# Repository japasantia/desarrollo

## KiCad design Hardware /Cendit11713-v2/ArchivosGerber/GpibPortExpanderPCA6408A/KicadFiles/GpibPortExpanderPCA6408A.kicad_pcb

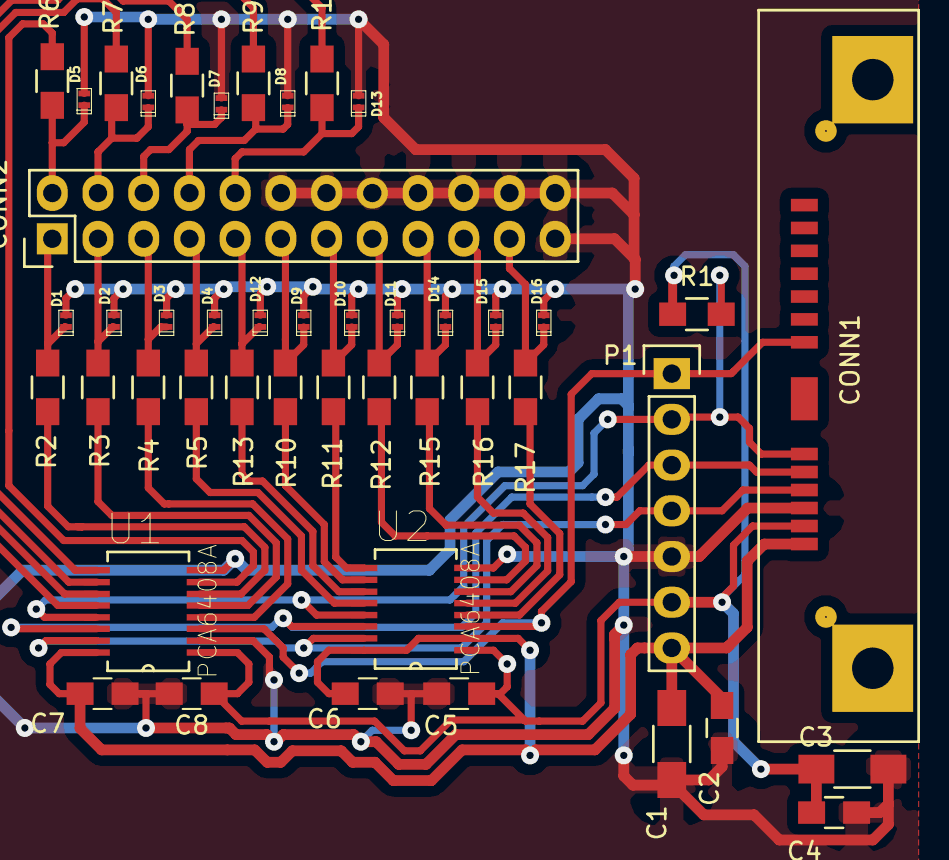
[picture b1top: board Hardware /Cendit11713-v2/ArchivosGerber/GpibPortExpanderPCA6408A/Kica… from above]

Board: 2 copper layers, 46 parts (0 on the bottom side), 39 nets.

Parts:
C1, C3: 1uF; C_1206_HandSoldering
C2, C4, C5, C6, C7, C8: 0.1uF; C_0805_HandSoldering
CONN1: I2C_BUS; SLIMLINE_SATA_PLUG_7P_6P
CONN2: GPIB_CONN; GPIB_HEADER_12X2P
D1, D2, D3, D4, D5, D6, D7, D8, D9, D10, D11, D12, D13, D14, D15, D16: SPHV24; SPHV24-SOD882
P1: CONN_01X07; Pin_Header_Straight_1x07
R1: R; R_0805_HandSoldering
R2, R3, R4, R5, R6, R7, R8, R9, R10, R11, R12, R13, R14, R15, R16, R17: RB; R_0805_HandSoldering
U1, U2: PCA6408A; PCA6408A-SOP16

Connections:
+3V3: C3.1, C4.1, C6.1, C8.1, CONN1.2, P1.6, R1.1, U1.1, U2.1
+5V: C1.1, C2.1, C5.1, C7.1, CONN1.1, P1.7, U1.16, U2.2, U2.16
//INT: CONN1.6, P1.2, R1.2, U1.13, U2.13
//RESET: CONN1.7, P1.1, U1.3, U2.3
/ATN: CONN2.21, D16.1, R17.1
/D0: CONN2.1, D1.1, R2.1
/D1: CONN2.3, D2.1, R3.1
/D2: CONN2.5, D3.1, R4.1
/D3: CONN2.7, D4.1, R5.1
/D4: CONN2.2, D5.1, R6.1
/D5: CONN2.4, D6.1, R7.1
/D6: CONN2.6, D7.1, R8.1
/D7: CONN2.8, D8.1, R9.1
/DAV: CONN2.11, D9.1, R10.1
/EOI: CONN2.9, D12.1, R13.1
/IFC: CONN2.17, D14.1, R15.1
/NDAC: CONN2.15, D11.1, R12.1
/NRFD: CONN2.13, D10.1, R11.1
/PATN: R17.2, U2.4
/PD0: R2.2, U1.6
/PD1: R3.2, U1.5
/PD2: R4.2, U1.4
/PD3: R5.2, U2.12
/PD4: R6.2, U1.7
/PD5: R7.2, U1.9
/PD6: R8.2, U1.10
/PD7: R9.2, U1.11
/PDAV: R12.2, U2.7
/PEOI: R13.2, U2.11
/PIFC: R15.2, U2.6
/PNDAC: R10.2, U2.10
/PNRFD: R11.2, U2.9
/PREN: R14.2, U1.12
/PSRQ: R16.2, U2.5
/REN: CONN2.10, D13.1, R14.1
/SCL: CONN1.5, P1.3, U1.14, U2.14
/SDA: CONN1.4, P1.4, U1.15, U2.15
/SRQ: CONN2.19, D15.1, R16.1
GNDD: C1.2, C2.2, C3.2, C4.2, C5.2, C6.2, C7.2, C8.2, CONN1.3, CONN2.12, CONN2.14, CONN2.16, CONN2.18, CONN2.20, CONN2.22, CONN2.23, CONN2.24, D1.2, D2.2, D3.2, D4.2, D5.2, D6.2, D7.2, D8.2, D9.2, D10.2, D11.2, D12.2, D13.2, D14.2, D15.2, D16.2, P1.5, U1.2, U1.8, U2.8

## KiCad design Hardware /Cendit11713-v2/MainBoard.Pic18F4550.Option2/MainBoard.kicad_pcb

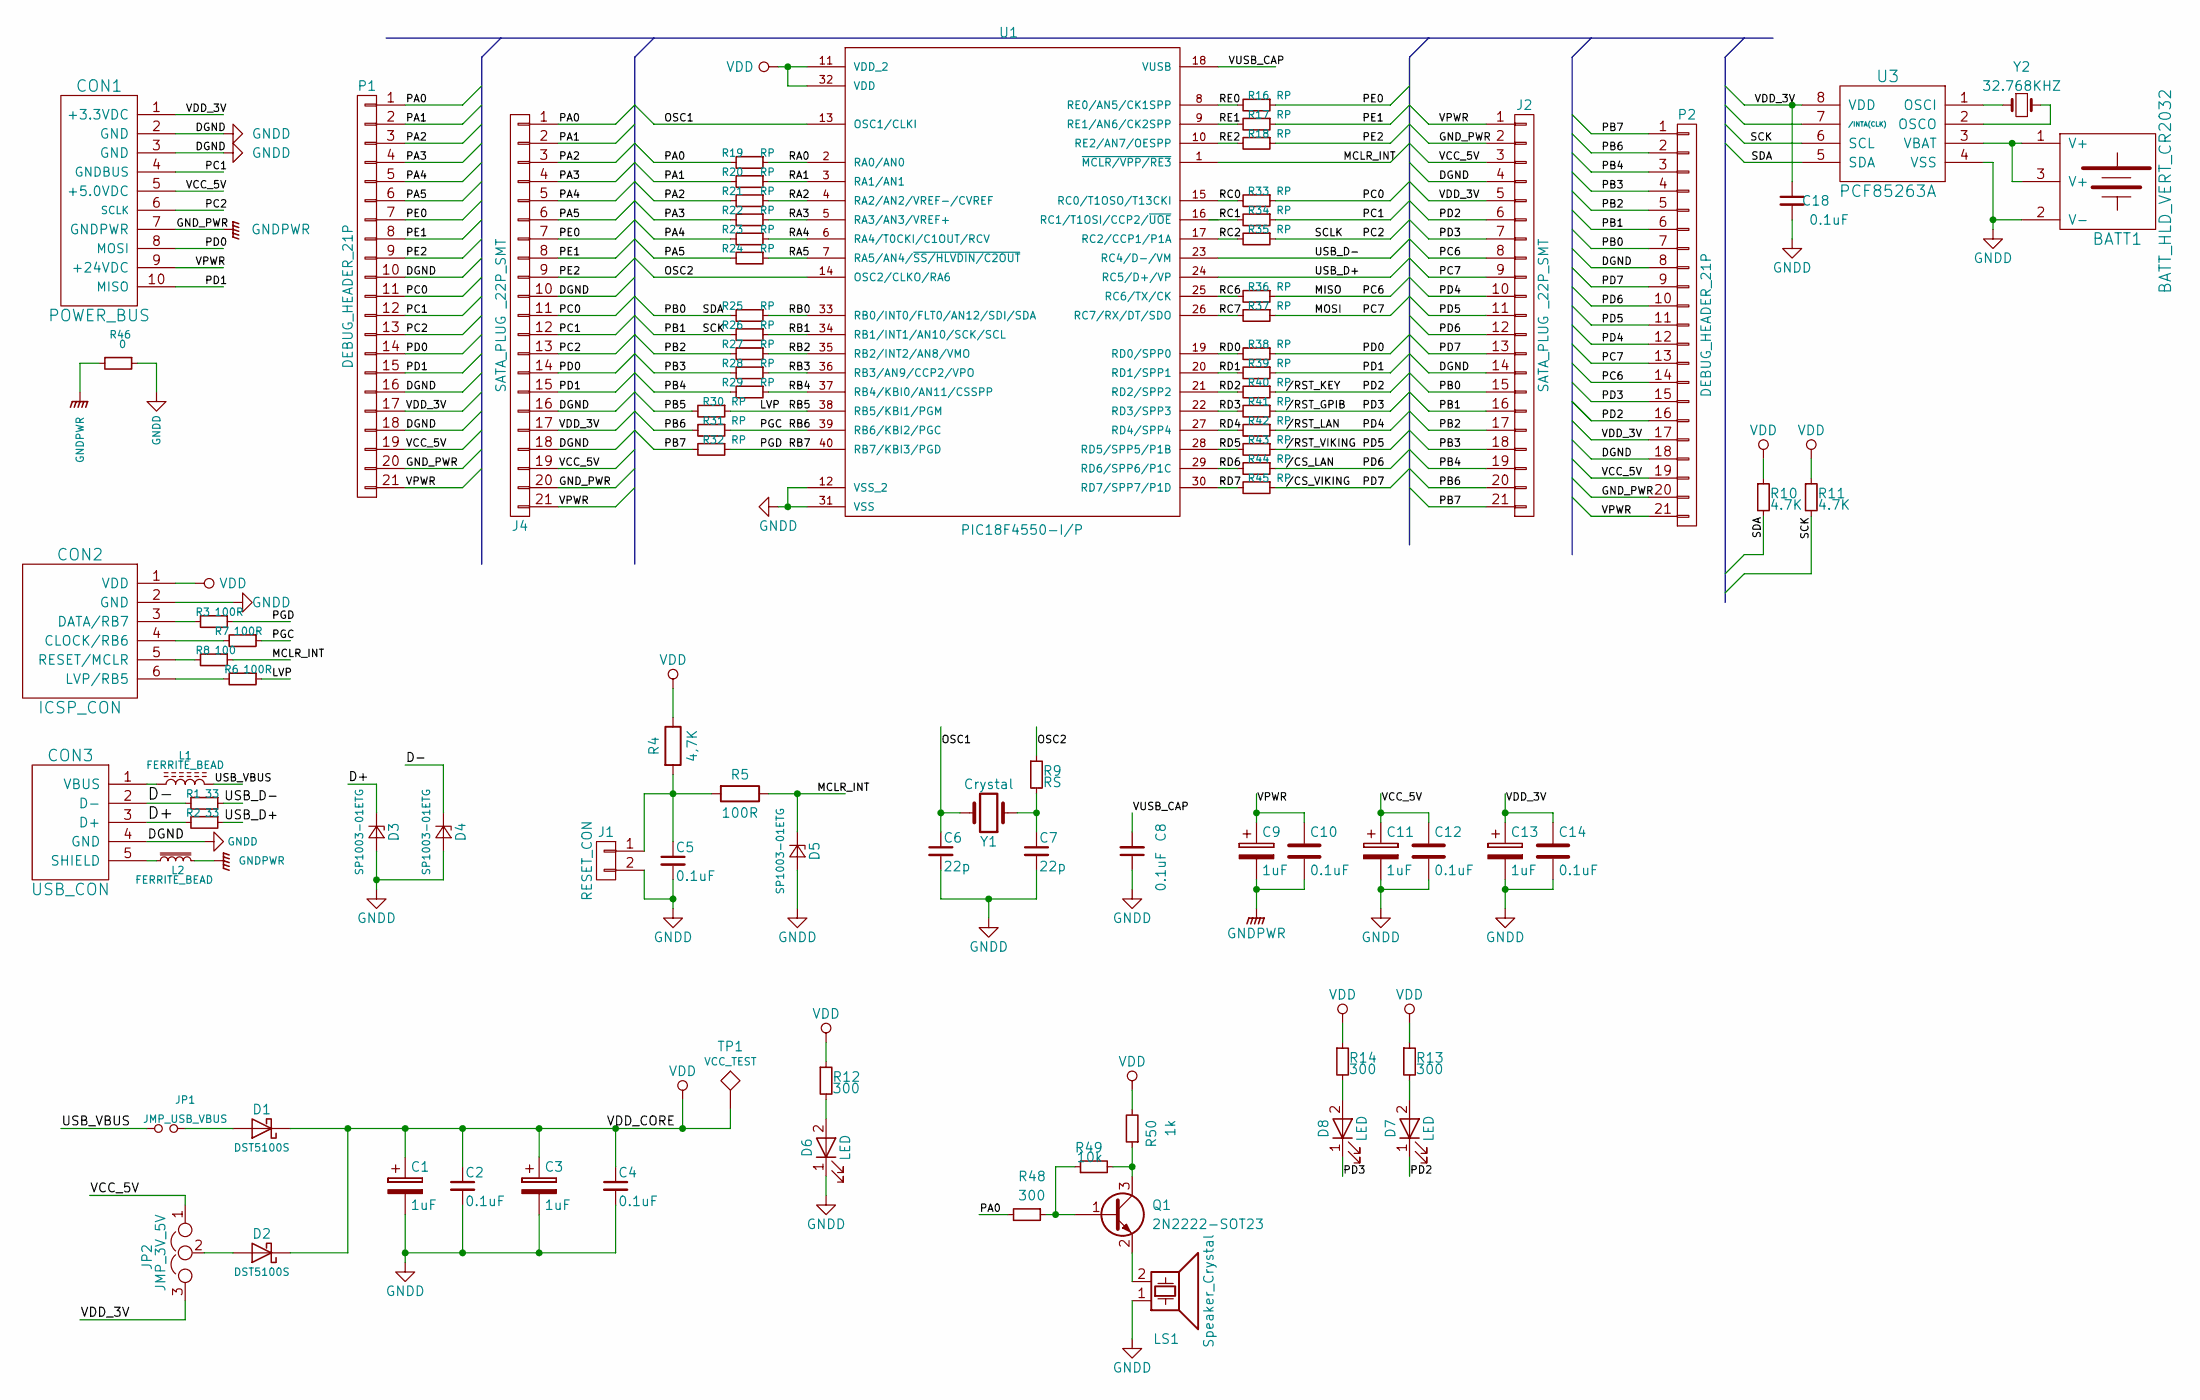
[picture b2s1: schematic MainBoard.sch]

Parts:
BATT1: BATT_HLD_VERT_CR2032; BATTERY_HOLDER_VERT_CR2032
C1, C3, C9, C11, C13: 1uF; C_1206_HandSoldering
C2, C4, C5, C10, C12, C14, C18: 0.1uF; C_0805_HandSoldering
C6, C7: 22p; C_0805_HandSoldering
C8: 0.1uF; C_1206_HandSoldering
CON1: POWER_BUS
CON2: ICSP_CON; Pin_Header_Straight_2x03
CON3: USB_CON; USB_SMT_B
D1, D2: DST5100S; DST5100S-TO-277B
D3, D4, D5: SP1003-01ETG
D6, D7, D8: LED; LED_0805
J1: RESET_CON; Pin_Header_Straight_1x02_Pitch2.54mm
J2, J4: SATA_PLUG _22P_SMT; SATA_PLUG_22P_SMT
JP1: JMP_USB_VBUS; Pin_Header_Straight_1x02_Pitch2.54mm
JP2: JMP_3V_5V; Pin_Header_Straight_1x03
L1, L2: FERRITE_BEAD; L_Axial_L5.3mm_D2.2mm_P2.54mm_Vertical_Vishay_IM-1
LS1: Speaker_Crystal; MagneticBuzzer_Kingstate_KCG0601
P1, P2: DEBUG_HEADER_21P; DEBUG_PIN_HEADER_21P
Q1: 2N2222-SOT23
R1, R2: 33; R_0603_HandSoldering
R3, R5, R6, R7: 100R; R_0805_HandSoldering
R4: 4,7K; R_0805_HandSoldering
R8: 100; R_0805_HandSoldering
R9: RS; R_0805_HandSoldering
R10, R11: 4.7K; R_0805_HandSoldering
R12, R13, R14: 300; R_0805_HandSoldering
R16, R17, R18, R19, R20, R21, R22, R23, R24, R25, R26, R27, R28, R29, R30, R31, R32, R33, R34, R35, R36, R37, R38, R39, R40, R41, R42, R43, R44, R45: RP; R_0805_HandSoldering
R46: 0; R_0805_HandSoldering
R48: 300; R_0603_HandSoldering
R49: 10k; R_0603_HandSoldering
R50: 1k; R_0603_HandSoldering
TP1: VCC_TEST
U1: PIC18F4550-I/P; PIC18F4550-PDIP
U3: PCF85263A; PCF85263A_SO8
Y1: Crystal; Crystal_HC49-4H_Vertical
Y2: 32.768KHZ; Crystal_C26-LF_d2.1mm_l6.5mm_Vertical

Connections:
//CS_LAN: J2.12, P2.10, R44.1
//CS_VIKING: J2.13, P2.9, R45.1
//RST_GPIB: D8.1 (K), J2.7, P2.15, R41.1
//RST_KEY: D7.1 (K), J2.6, P2.16, R40.1
//RST_LAN: J2.10, P2.12, R42.1
//RST_VIKING: J2.11, P2.11, R43.1
/D+: CON3.3 (D+), D3.1 (K), R2.2
/D-: CON3.2 (D-), D4.1 (K), R1.2
/LVP: R6.1, R30.1, U1.38 (RB5/KBI1/PGM)
/MCLR_INT: D5.1 (K), R5.1, R8.1, U1.1 (~MCLR/VPP/RE3)
/MISO: J2.8, P2.14, R36.1
/MOSI: J2.9, P2.13, R37.1
/OSC1: C6.1, U1.13 (OSC1/CLKI), Y1.2
/OSC2: R9.1, U1.14 (OSC2/CLKO/RA6)
/PA0: J4.1, P1.1, R19.2, R48.2
/PA1: J4.2, P1.2, R20.2
/PA2: J4.3, P1.3, R21.2
/PA3: J4.4, P1.4, R22.2
/PA4: J4.5, P1.5, R23.2
/PA5: J4.6, P1.6, R24.2
/PB0: J2.15, P2.7, R10.2, R25.2, U3.5 (SDA)
/PB1: J2.16, P2.6, R11.2, R26.2, U3.6 (SCL)
/PB2: J2.17, P2.5, R27.2
/PB3: J2.18, P2.4, R28.2
/PB4: J2.19, P2.3, R29.2
/PB5: R30.2
/PB6: J2.20, P2.2, R31.2
/PB7: J2.21, P2.1, R32.2
/PC0: J4.11, P1.11, R33.1
/PC1: CON1.4 (GNDBUS), J4.12, P1.12, R34.1
/PC2: CON1.6 (SCLK), J4.13, P1.13, R35.1
/PD0: CON1.8 (MOSI), J4.14, P1.14, R38.1
/PD1: CON1.10 (MISO), J4.15, P1.15, R39.1
/PE0: J4.7, P1.7, R16.1
/PE1: J4.8, P1.8, R17.1
/PE2: J4.9, P1.9, R18.1
/PGC: R7.1, R31.1, U1.39 (RB6/KBI2/PGC)
/PGD: R3.1, R32.1, U1.40 (RB7/KBI3/PGD)
/RA0: R19.1, U1.2 (RA0/AN0)
/RA1: R20.1, U1.3 (RA1/AN1)
/RA2: R21.1, U1.4 (RA2/AN2/VREF-/CVREF)
/RA3: R22.1, U1.5 (RA3/AN3/VREF+)
/RA4: R23.1, U1.6 (RA4/T0CKI/C1OUT/RCV)
/RA5: R24.1, U1.7 (RA5/AN4/~SS/HLVDIN/C2OUT)
/RB0: R25.1, U1.33 (RB0/INT0/FLT0/AN12/SDI/SDA)
/RB1: R26.1, U1.34 (RB1/INT1/AN10/SCK/SCL)
/RB2: R27.1, U1.35 (RB2/INT2/AN8/VMO)
/RB3: R28.1, U1.36 (RB3/AN9/CCP2/VPO)
/RB4: R29.1, U1.37 (RB4/KBI0/AN11/CSSPP)
/RC0: R33.2, U1.15 (RC0/T1OSO/T13CKI)
/RC1: R34.2, U1.16 (RC1/T1OSI/CCP2/~UOE)
/RC2: R35.2, U1.17 (RC2/CCP1/P1A)
/RC6: R36.2, U1.25 (RC6/TX/CK)
/RC7: R37.2, U1.26 (RC7/RX/DT/SDO)
/RD0: R38.2, U1.19 (RD0/SPP0)
/RD1: R39.2, U1.20 (RD1/SPP1)
/RD2: R40.2, U1.21 (RD2/SPP2)
/RD3: R41.2, U1.22 (RD3/SPP3)
/RD4: R42.2, U1.27 (RD4/SPP4)
/RD5: R43.2, U1.28 (RD5/SPP5/P1B)
/RD6: R44.2, U1.29 (RD6/SPP6/P1C)
/RD7: R45.2, U1.30 (RD7/SPP7/P1D)
/RE0: R16.2, U1.8 (RE0/AN5/CK1SPP)
/RE1: R17.2, U1.9 (RE1/AN6/CK2SPP)
/RE2: R18.2, U1.10 (RE2/AN7/OESPP)
/USB_D+: R2.1, U1.24 (RC5/D+/VP)
/USB_D-: R1.1, U1.23 (RC4/D-/VM)
/USB_VBUS: JP1.1, L1.2
/VCC_5V: C11.1, C12.1, CON1.5 (+5.0VDC), J2.3, J4.19, JP2.1, P1.19, P2.19
/VDD_3V: C13.1, C14.1, C18.1, CON1.1 (+3.3VDC), J2.5, J4.17, JP2.3, P1.17, P2.17, U3.8 (VDD)
/VPWR: C9.1, C10.1, CON1.9 (+24VDC), J2.1, J4.21, P1.21, P2.21
/VUSB_CAP: C8.2, U1.18 (VUSB)
GNDD: BATT1.2 (V-), C1.2, C2.2, C3.2, C4.2, C5.2, C6.2, C7.2, C8.1, C11.2, C12.2, C13.2, C14.2, C18.2, CON1.2 (GND), CON1.3 (GND), CON2.2 (GND), CON3.4 (GND), D3.2 (A), D4.2 (A), D5.2 (A), D6.1 (K), J1.2, J2.4, J2.14, J4.10, J4.16, J4.18, LS1.1, P1.10, P1.16, P1.18, P2.8, P2.18, R46.1, U1.12 (VSS_2), U1.31 (VSS), U3.4 (VSS)
GNDPWR: C9.2, C10.2, CON1.7 (GNDPWR), J2.2, J4.20, L2.2, P1.20, P2.20, R46.2
unnamed: BATT1.1 (V+), BATT1.3 (V+), U3.3 (VBAT)
unnamed: C5.1, J1.1, R4.2, R5.2
unnamed: C7.1, R9.2, Y1.1
unnamed: CON2.3 (DATA/RB7), R3.2
unnamed: CON2.4 (CLOCK/RB6), R7.2
unnamed: CON2.5 (RESET/MCLR), R8.2
unnamed: CON2.6 (LVP/RB5), R6.2
unnamed: CON3.1 (VBUS), L1.1
unnamed: CON3.5 (SHIELD), L2.1
unnamed: D1.2 (A), JP1.2
unnamed: D2.2 (A), JP2.2
unnamed: D6.2 (A), R12.2
unnamed: D7.2 (A), R13.2
unnamed: D8.2 (A), R14.2
unnamed: LS1.2, Q1.2 (E)
unnamed: Q1.1 (B), R48.1, R49.1
unnamed: Q1.3 (C), R49.2, R50.1
unnamed: U3.1 (OSCI), Y2.1
unnamed: U3.2 (OSCO), Y2.2
VDD: C1.1, C2.1, C3.1, C4.1, CON2.1 (VDD), D1.1 (K), D2.1 (K), R4.1, R10.1, R11.1, R12.1, R13.1, R14.1, R50.2, TP1.1, U1.11 (VDD_2), U1.32 (VDD)

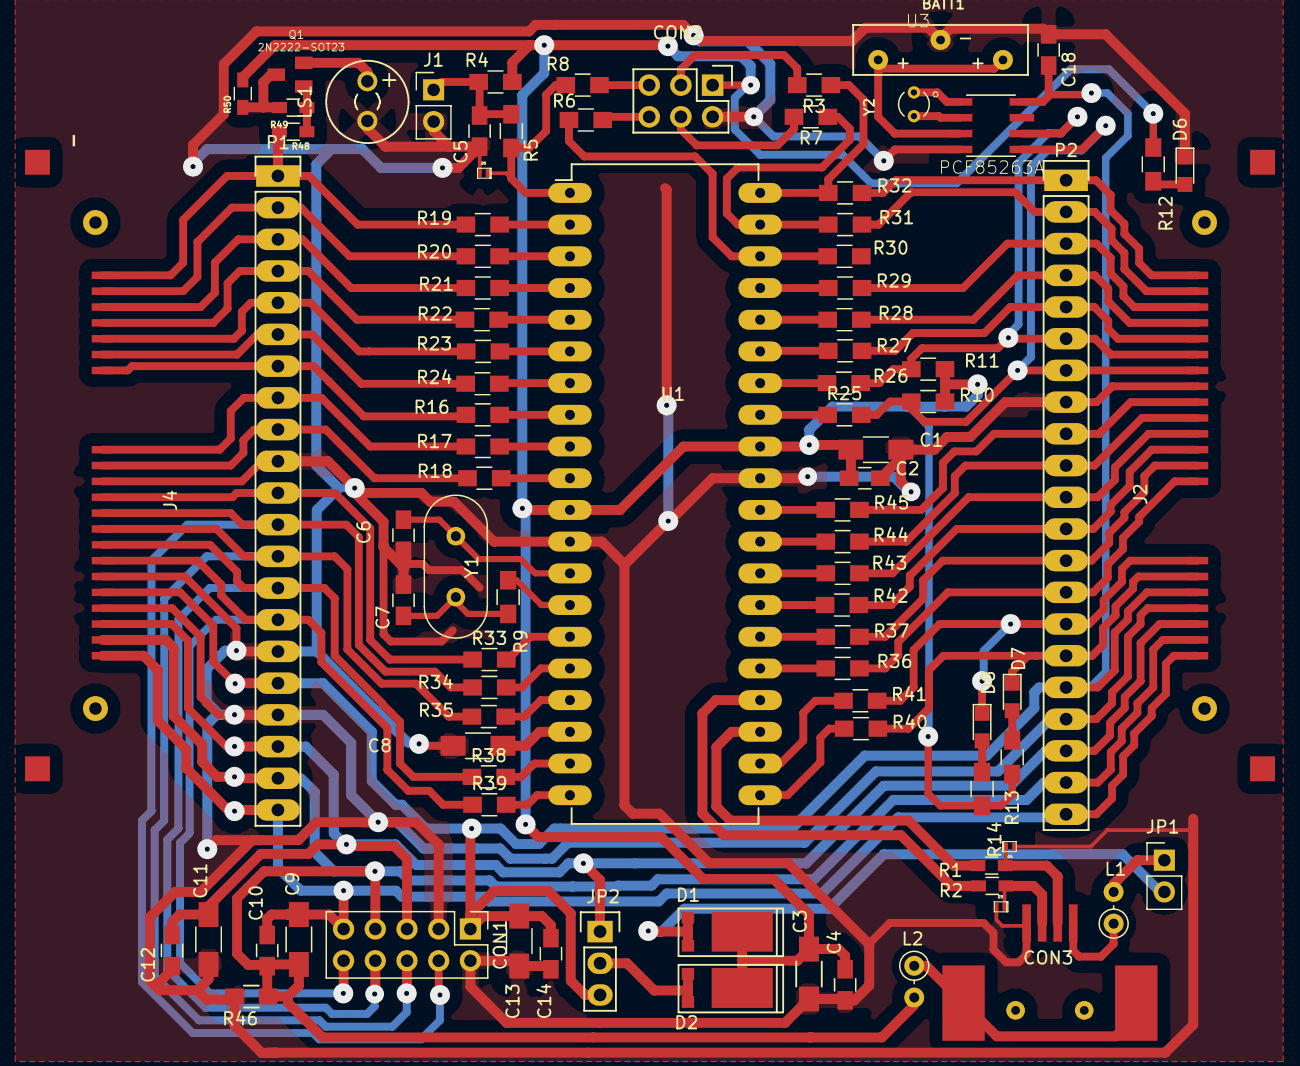
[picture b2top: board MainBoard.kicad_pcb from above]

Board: 2 copper layers, 90 parts (0 on the bottom side), 93 nets.

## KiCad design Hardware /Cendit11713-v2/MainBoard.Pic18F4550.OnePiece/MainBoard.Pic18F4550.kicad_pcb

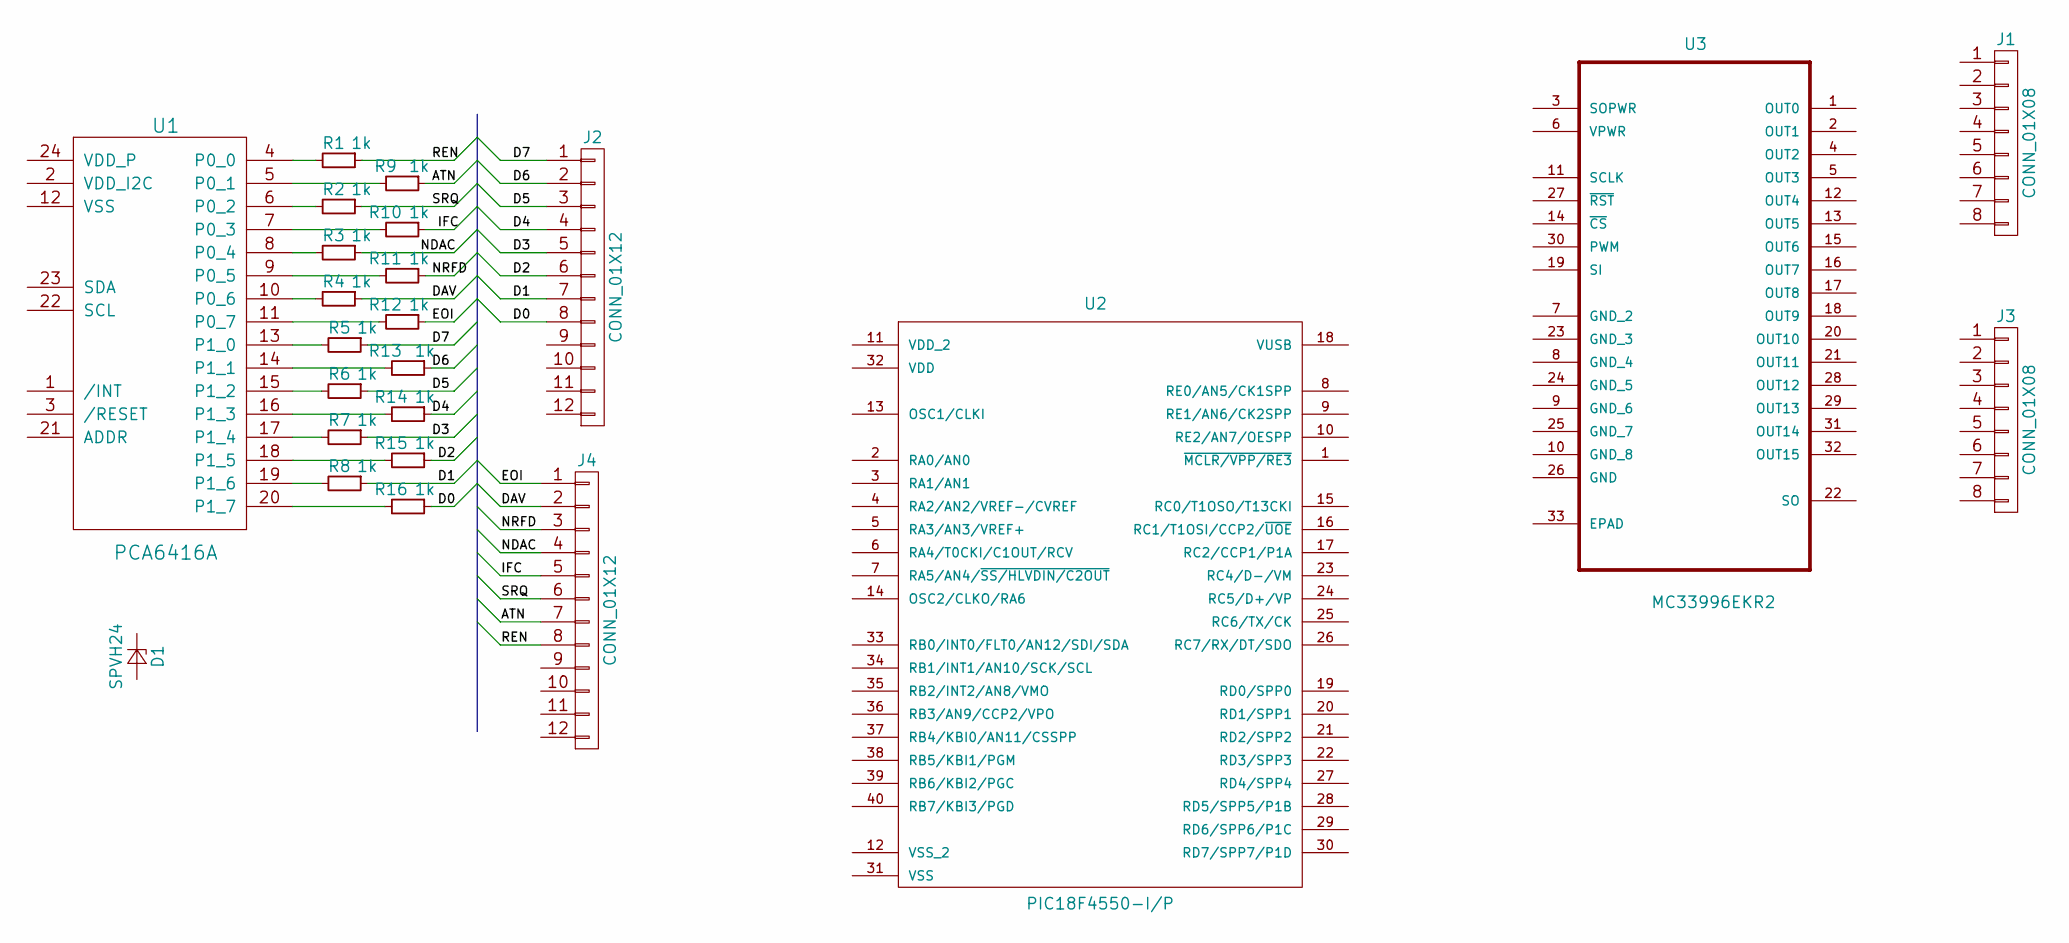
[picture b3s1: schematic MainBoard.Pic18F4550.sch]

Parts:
D1: SPVH24; SPHV24-SOD882
J1, J3: CONN_01X08; Pin_Header_Straight_1x08_Pitch2.54mm
J2, J4: CONN_01X12; Pin_Header_Straight_1x12_Pitch2.54mm
R1, R2, R3, R4, R5, R6, R7, R8, R9, R10, R11, R12, R13, R14, R15, R16: 1k; R_0805_HandSoldering
U1: PCA6416A; PCA6416A-TSSOP24
U2: PIC18F4550-I/P; PIC18F4550-PDIP
U3: MC33996EKR2; MC33996-SOIC32

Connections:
/ATN: J4.7, R9.1
/D0: J2.8, R16.1
/D1: J2.7, R8.1
/D2: J2.6, R15.1
/D3: J2.5, R7.1
/D4: J2.4, R14.1
/D5: J2.3, R6.1
/D6: J2.2, R13.1
/D7: J2.1, R5.1
/DAV: J4.2, R4.1
/EOI: J4.1, R12.1
/IFC: J4.5, R10.1
/NDAC: J4.4, R3.1
/NRFD: J4.3, R11.1
/REN: J4.8, R1.1
/SRQ: J4.6, R2.1
unnamed: R1.2, U1.4 (P0_0)
unnamed: R2.2, U1.6 (P0_2)
unnamed: R3.2, U1.8 (P0_4)
unnamed: R4.2, U1.10 (P0_6)
unnamed: R5.2, U1.13 (P1_0)
unnamed: R6.2, U1.15 (P1_2)
unnamed: R7.2, U1.17 (P1_4)
unnamed: R8.2, U1.19 (P1_6)
unnamed: R9.2, U1.5 (P0_1)
unnamed: R10.2, U1.7 (P0_3)
unnamed: R11.2, U1.9 (P0_5)
unnamed: R12.2, U1.11 (P0_7)
unnamed: R13.2, U1.14 (P1_1)
unnamed: R14.2, U1.16 (P1_3)
unnamed: R15.2, U1.18 (P1_5)
unnamed: R16.2, U1.20 (P1_7)

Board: 2 copper layers, 24 parts (0 on the bottom side), 32 nets, no tracks yet.

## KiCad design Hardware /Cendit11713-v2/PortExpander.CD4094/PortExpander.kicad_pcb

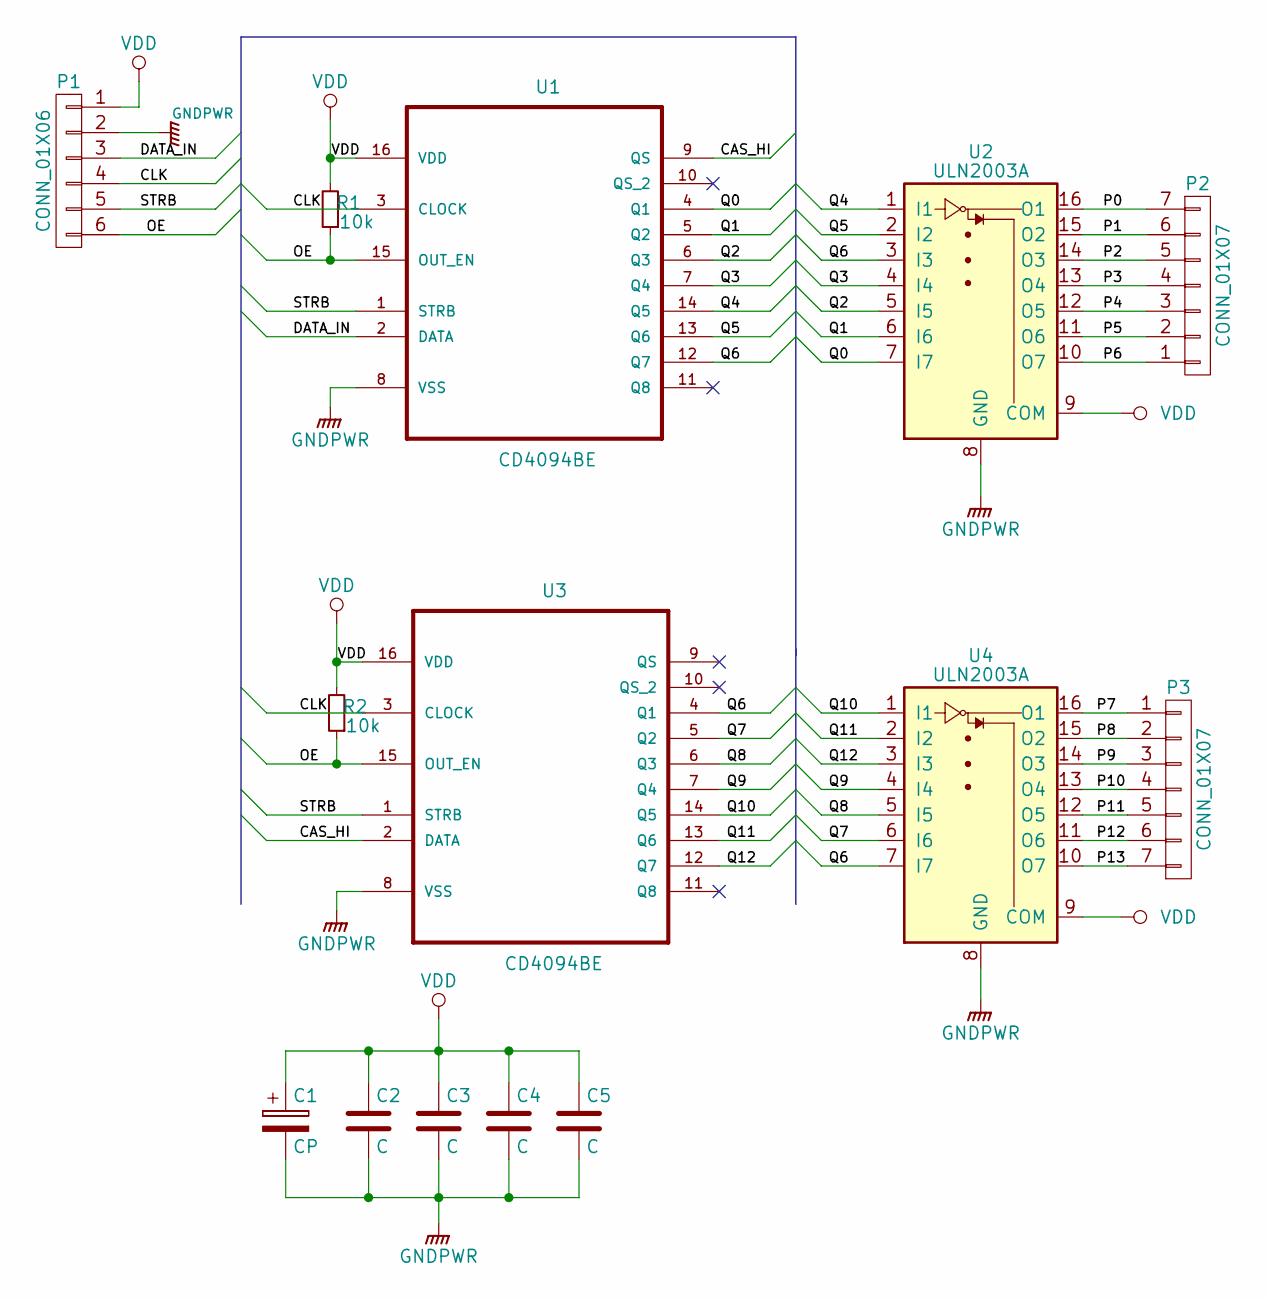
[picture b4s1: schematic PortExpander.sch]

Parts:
C1: CP; C_0805_HandSoldering
C2, C3, C4, C5: C; C_0805_HandSoldering
P1: CONN_01X06; Pin_Header_Straight_1x06
P2, P3: CONN_01X07; Pin_Header_Straight_1x07
R1, R2: 10k; R_0805_HandSoldering
U1, U3: CD4094BE; CD4094-DIP16
U2, U4: ULN2003A; ULN2003-DIP16

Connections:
/CAS_HI: U1.9 (QS), U3.2 (DATA)
/CLK: P1.4, U1.3 (CLOCK), U3.3 (CLOCK)
/DATA_IN: P1.3, U1.2 (DATA)
/OE: P1.6, R1.1, R2.1, U1.15 (OUT_EN), U3.15 (OUT_EN)
/P0: P2.7, U2.16 (O1)
/P1: P2.6, U2.15 (O2)
/P2: P2.5, U2.14 (O3)
/P3: P2.4, U2.13 (O4)
/P4: P2.3, U2.12 (O5)
/P5: P2.2, U2.11 (O6)
/P6: P2.1, U2.10 (O7)
/P7: P3.1, U4.16 (O1)
/P8: P3.2, U4.15 (O2)
/P9: P3.3, U4.14 (O3)
/P10: P3.4, U4.13 (O4)
/P11: P3.5, U4.12 (O5)
/P12: P3.6, U4.11 (O6)
/P13: P3.7, U4.10 (O7)
/Q0: U1.4 (Q1), U2.7 (I7)
/Q1: U1.5 (Q2), U2.6 (I6)
/Q2: U1.6 (Q3), U2.5 (I5)
/Q3: U1.7 (Q4), U2.4 (I4)
/Q4: U1.14 (Q5), U2.1 (I1)
/Q5: U1.13 (Q6), U2.2 (I2)
/Q6: U1.12 (Q7), U2.3 (I3), U3.4 (Q1), U4.7 (I7)
/Q7: U3.5 (Q2), U4.6 (I6)
/Q8: U3.6 (Q3), U4.5 (I5)
/Q9: U3.7 (Q4), U4.4 (I4)
/Q10: U3.14 (Q5), U4.1 (I1)
/Q11: U3.13 (Q6), U4.2 (I2)
/Q12: U3.12 (Q7), U4.3 (I3)
/STRB: P1.5, U1.1 (STRB), U3.1 (STRB)
GNDPWR: C1.2, C2.2, C3.2, C4.2, C5.2, P1.2, U1.8 (VSS), U2.8 (GND), U3.8 (VSS), U4.8 (GND)
VDD: C1.1, C2.1, C3.1, C4.1, C5.1, P1.1, R1.2, R2.2, U1.16 (VDD), U2.9 (COM), U3.16 (VDD), U4.9 (COM)

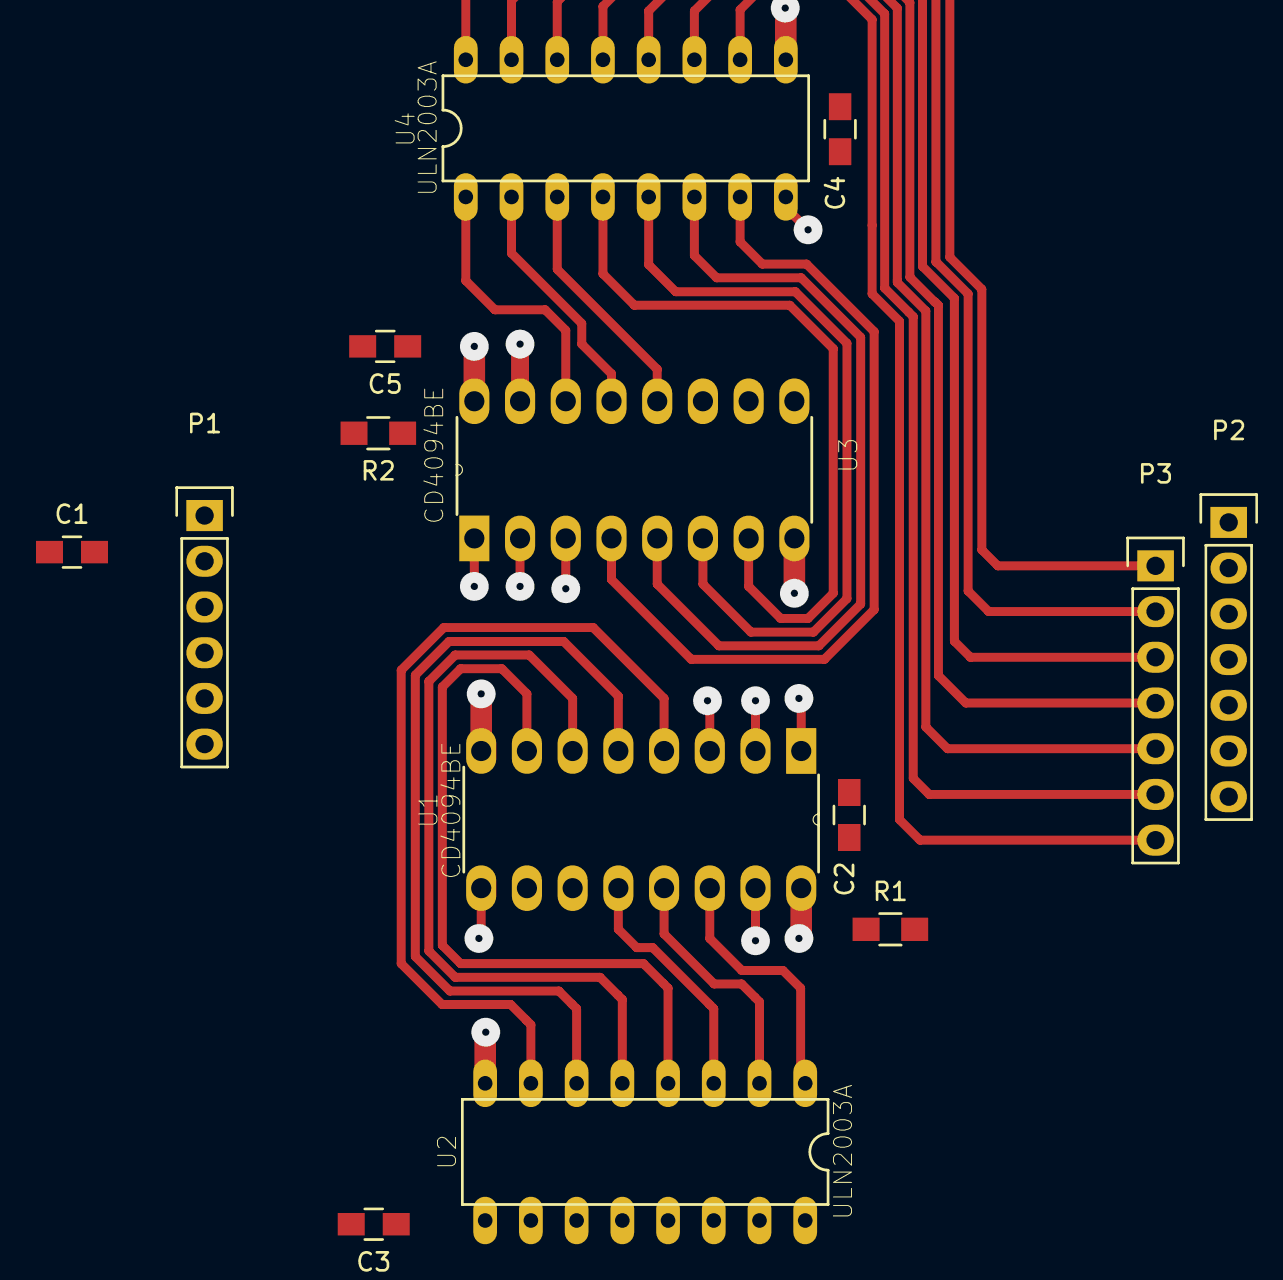
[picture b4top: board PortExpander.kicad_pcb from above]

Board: 2 copper layers, 14 parts (0 on the bottom side), 34 nets.

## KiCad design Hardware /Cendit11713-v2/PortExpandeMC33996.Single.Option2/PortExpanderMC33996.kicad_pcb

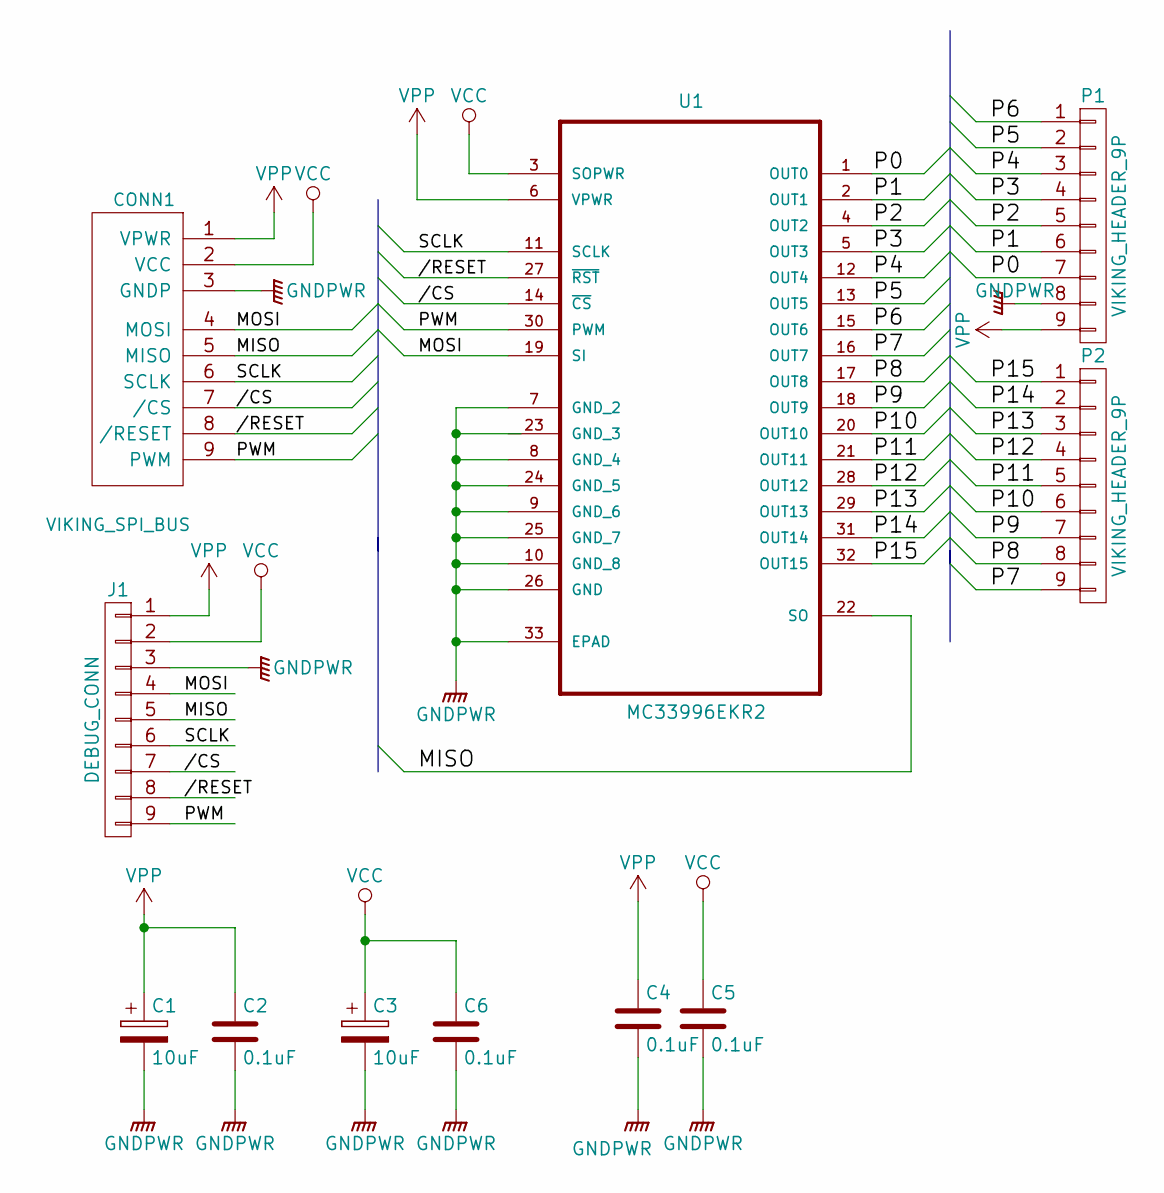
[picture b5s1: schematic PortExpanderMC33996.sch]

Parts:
C1, C3: 10uF; C_1206_HandSoldering
C2, C4, C5, C6: 0.1uF; C_0805_HandSoldering
CONN1: VIKING_SPI_BUS; SLIMLINE_SATA_PLUG_7P_6P
J1: DEBUG_CONN; Pin_Header_Straight_1x09
P1, P2: VIKING_HEADER_9P; Pin_Header_Straight_1x09
U1: MC33996EKR2

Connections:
//CS: CONN1.7 (/CS), J1.7, U1.14 (~CS)
//RESET: CONN1.8 (/RESET), J1.8, U1.27 (~RST)
/MISO: CONN1.5 (MISO), J1.5, U1.22 (SO)
/MOSI: CONN1.4 (MOSI), J1.4, U1.19 (SI)
/P0: P1.7, U1.1 (OUT0)
/P1: P1.6, U1.2 (OUT1)
/P2: P1.5, U1.4 (OUT2)
/P3: P1.4, U1.5 (OUT3)
/P4: P1.3, U1.12 (OUT4)
/P5: P1.2, U1.13 (OUT5)
/P6: P1.1, U1.15 (OUT6)
/P7: P2.9, U1.16 (OUT7)
/P8: P2.8, U1.17 (OUT8)
/P9: P2.7, U1.18 (OUT9)
/P10: P2.6, U1.20 (OUT10)
/P11: P2.5, U1.21 (OUT11)
/P12: P2.4, U1.28 (OUT12)
/P13: P2.3, U1.29 (OUT13)
/P14: P2.2, U1.31 (OUT14)
/P15: P2.1, U1.32 (OUT15)
/PWM: CONN1.9 (PWM), J1.9, U1.30 (PWM)
/SCLK: CONN1.6 (SCLK), J1.6, U1.11 (SCLK)
GNDPWR: C1.2, C2.2, C3.2, C4.2, C5.2, C6.2, CONN1.3 (GNDP), J1.3, P1.8, U1.7 (GND_2), U1.8 (GND_4), U1.9 (GND_6), U1.10 (GND_8), U1.24 (GND_5), U1.25 (GND_7), U1.26 (GND), U1.33 (EPAD)
VCC: C3.1, C5.1, C6.1, CONN1.2 (VCC), J1.2, U1.3 (SOPWR)
VPP: C1.1, C2.1, C4.1, CONN1.1 (VPWR), J1.1, P1.9, U1.6 (VPWR)

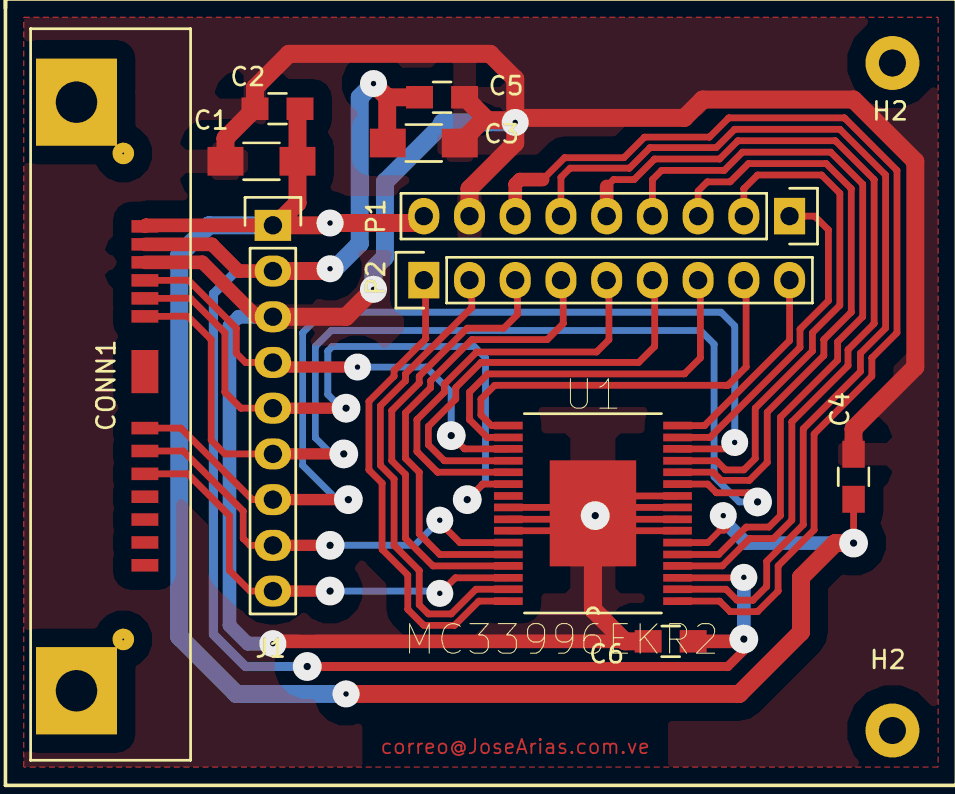
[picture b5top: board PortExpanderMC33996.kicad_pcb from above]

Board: 2 copper layers, 13 parts (0 on the bottom side), 25 nets.

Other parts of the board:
H2, H2#2: HOLE_3MM
